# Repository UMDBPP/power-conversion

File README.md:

# power-conversion
A set of power converters and other miscellaneous tools for high-altitude applications.

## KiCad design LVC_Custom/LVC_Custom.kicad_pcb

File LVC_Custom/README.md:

This board implements Low Voltage Cutoff (LVC) and reverse polarity protection funcitonality. It is currently designed for 1S, 2S, or 3S LiPo batteries. It features XT60 connectors and is relatively small. The FETs selected are P-Channel not the best on resistance but should be able to conduct at least 4A relatively easily.

View the schematic and board in your browser here: https://kicanvas.org/?github=https%3A%2F%2Fgithub.com%2FUMDBPP%2Fpower-conversion%2Ftree%2Fmain%2FLVC_Custom

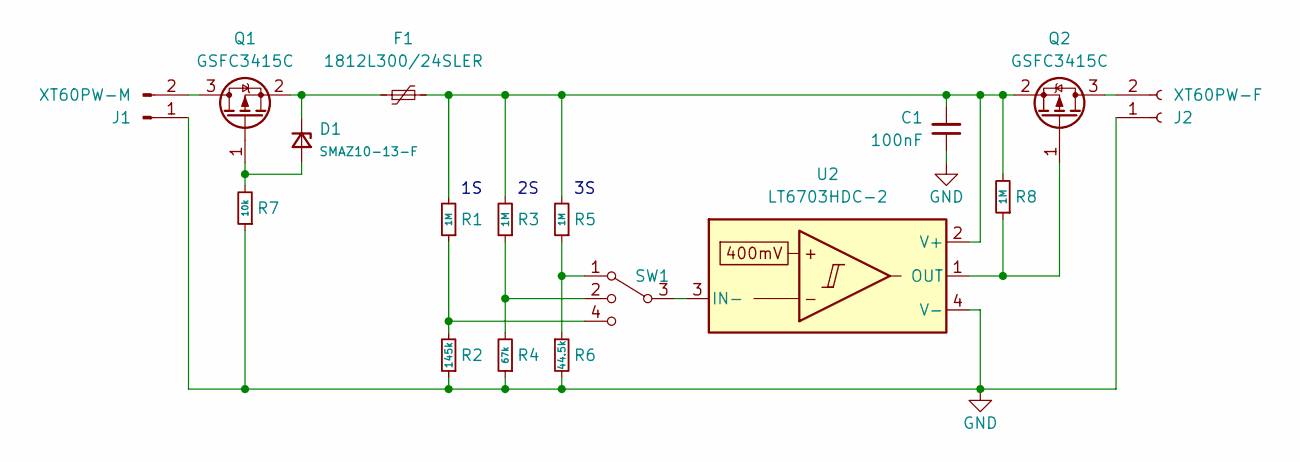
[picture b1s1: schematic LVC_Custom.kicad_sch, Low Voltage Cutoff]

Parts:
C1: 100nF; C_0603_1608Metric_Pad1.08x0.95mm_HandSolder
D1: SMAZ10-13-F; D_SMA_Handsoldering
F1: 1812L300/24SLER; Fuse_1812_4532Metric_Pad1.30x3.40mm_HandSolder
J1: XT60PW-M; AMASS_XT60PW-M_1x02_P7.20mm_Horizontal
J2: XT60PW-F; AMASS_XT60PW-F_1x02_P7.20mm_Horizontal
Q1, Q2: GSFC3415C; SOT-23-3
R1, R3, R5, R8: 1M; R_0603_1608Metric_Pad0.98x0.95mm_HandSolder
R2: 145k; R_0603_1608Metric_Pad0.98x0.95mm_HandSolder
R4: 67k; R_0603_1608Metric_Pad0.98x0.95mm_HandSolder
R6: 44.5k; R_0603_1608Metric_Pad0.98x0.95mm_HandSolder
R7: 10k; R_0603_1608Metric_Pad0.98x0.95mm_HandSolder
SW1: CUS-13TB; CUS-13TB_NDC
U2: LT6703HDC-2; DFN-3-1EP-2x2mm_P0.5mm_EP1x1.35mm

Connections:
GND: C1.1, J1.1, J2.1, R2.1, R4.1, R6.2, R7.1, U2.4 (V-)
unnamed: D1.2 (A), Q1.1 (G), R7.2
unnamed: D1.1 (K), F1.1, Q1.2 (S)
unnamed: J1.2, Q1.3 (D)
unnamed: J2.2, Q2.3 (D)
unnamed: Q2.1 (G), R8.1, U2.1 (OUT)
unnamed: C1.2, F1.2, Q2.2 (S), R1.2, R3.2, R5.2, R8.2, U2.2 (V+)
unnamed: R1.1, R2.2, SW1.4
unnamed: R3.1, R4.2, SW1.2
unnamed: R5.1, R6.1, SW1.1
unnamed: SW1.3, U2.3 (IN-)

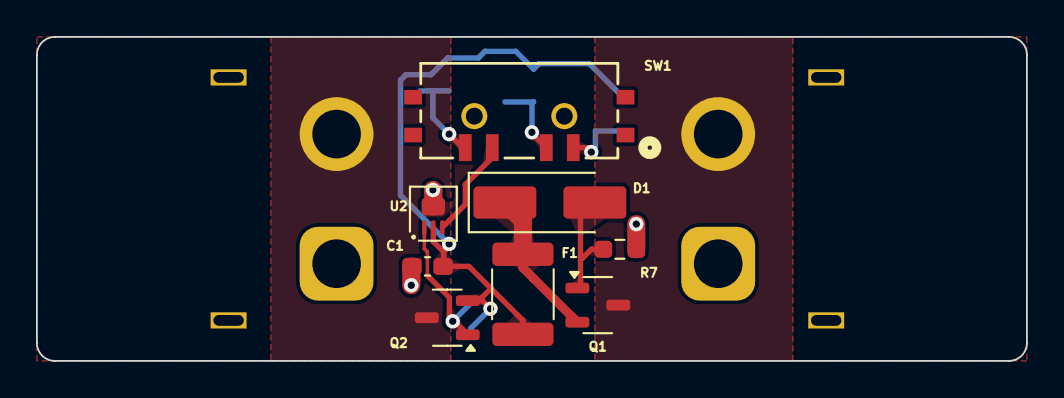
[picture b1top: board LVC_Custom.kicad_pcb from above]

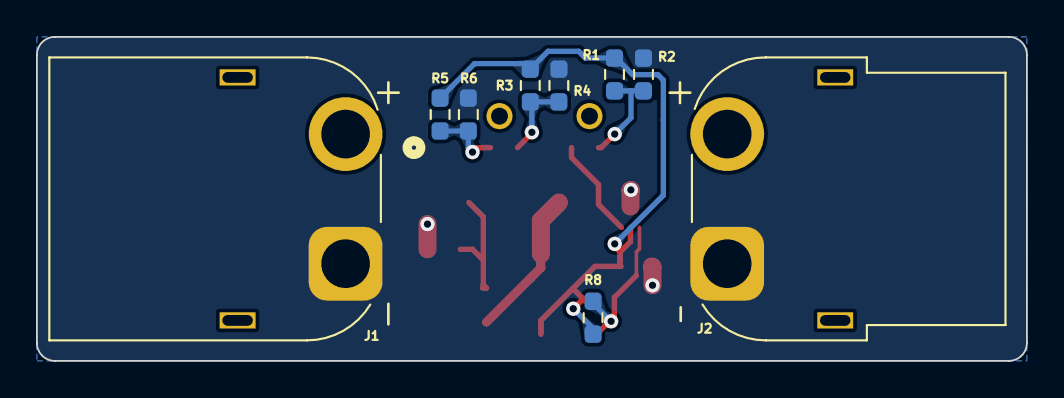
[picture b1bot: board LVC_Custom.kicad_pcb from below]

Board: 2 copper layers, 55.0 x 18.0 mm, 17 parts (9 on the bottom side), 11 nets.

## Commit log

2025-04-17 minimal LVC board, with fixed MOSFET
2025-04-17 added LVC read me
